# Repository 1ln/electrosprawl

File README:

Electrosprawl pcb

Hardware Design: 

Dan Olson 
Copyright 2019

This board is currently is testing phase, use at your own risk.

This board is designed as a testing platform for the cortex m4 samd51p20

Features:

Most pins broken out
Board can be attached to a raspberry pi 3 (board only, not pin header compatible)
Micro Sdcard slot
Micro usb available, 5v only

TODO:

Break out a few more pins if possible

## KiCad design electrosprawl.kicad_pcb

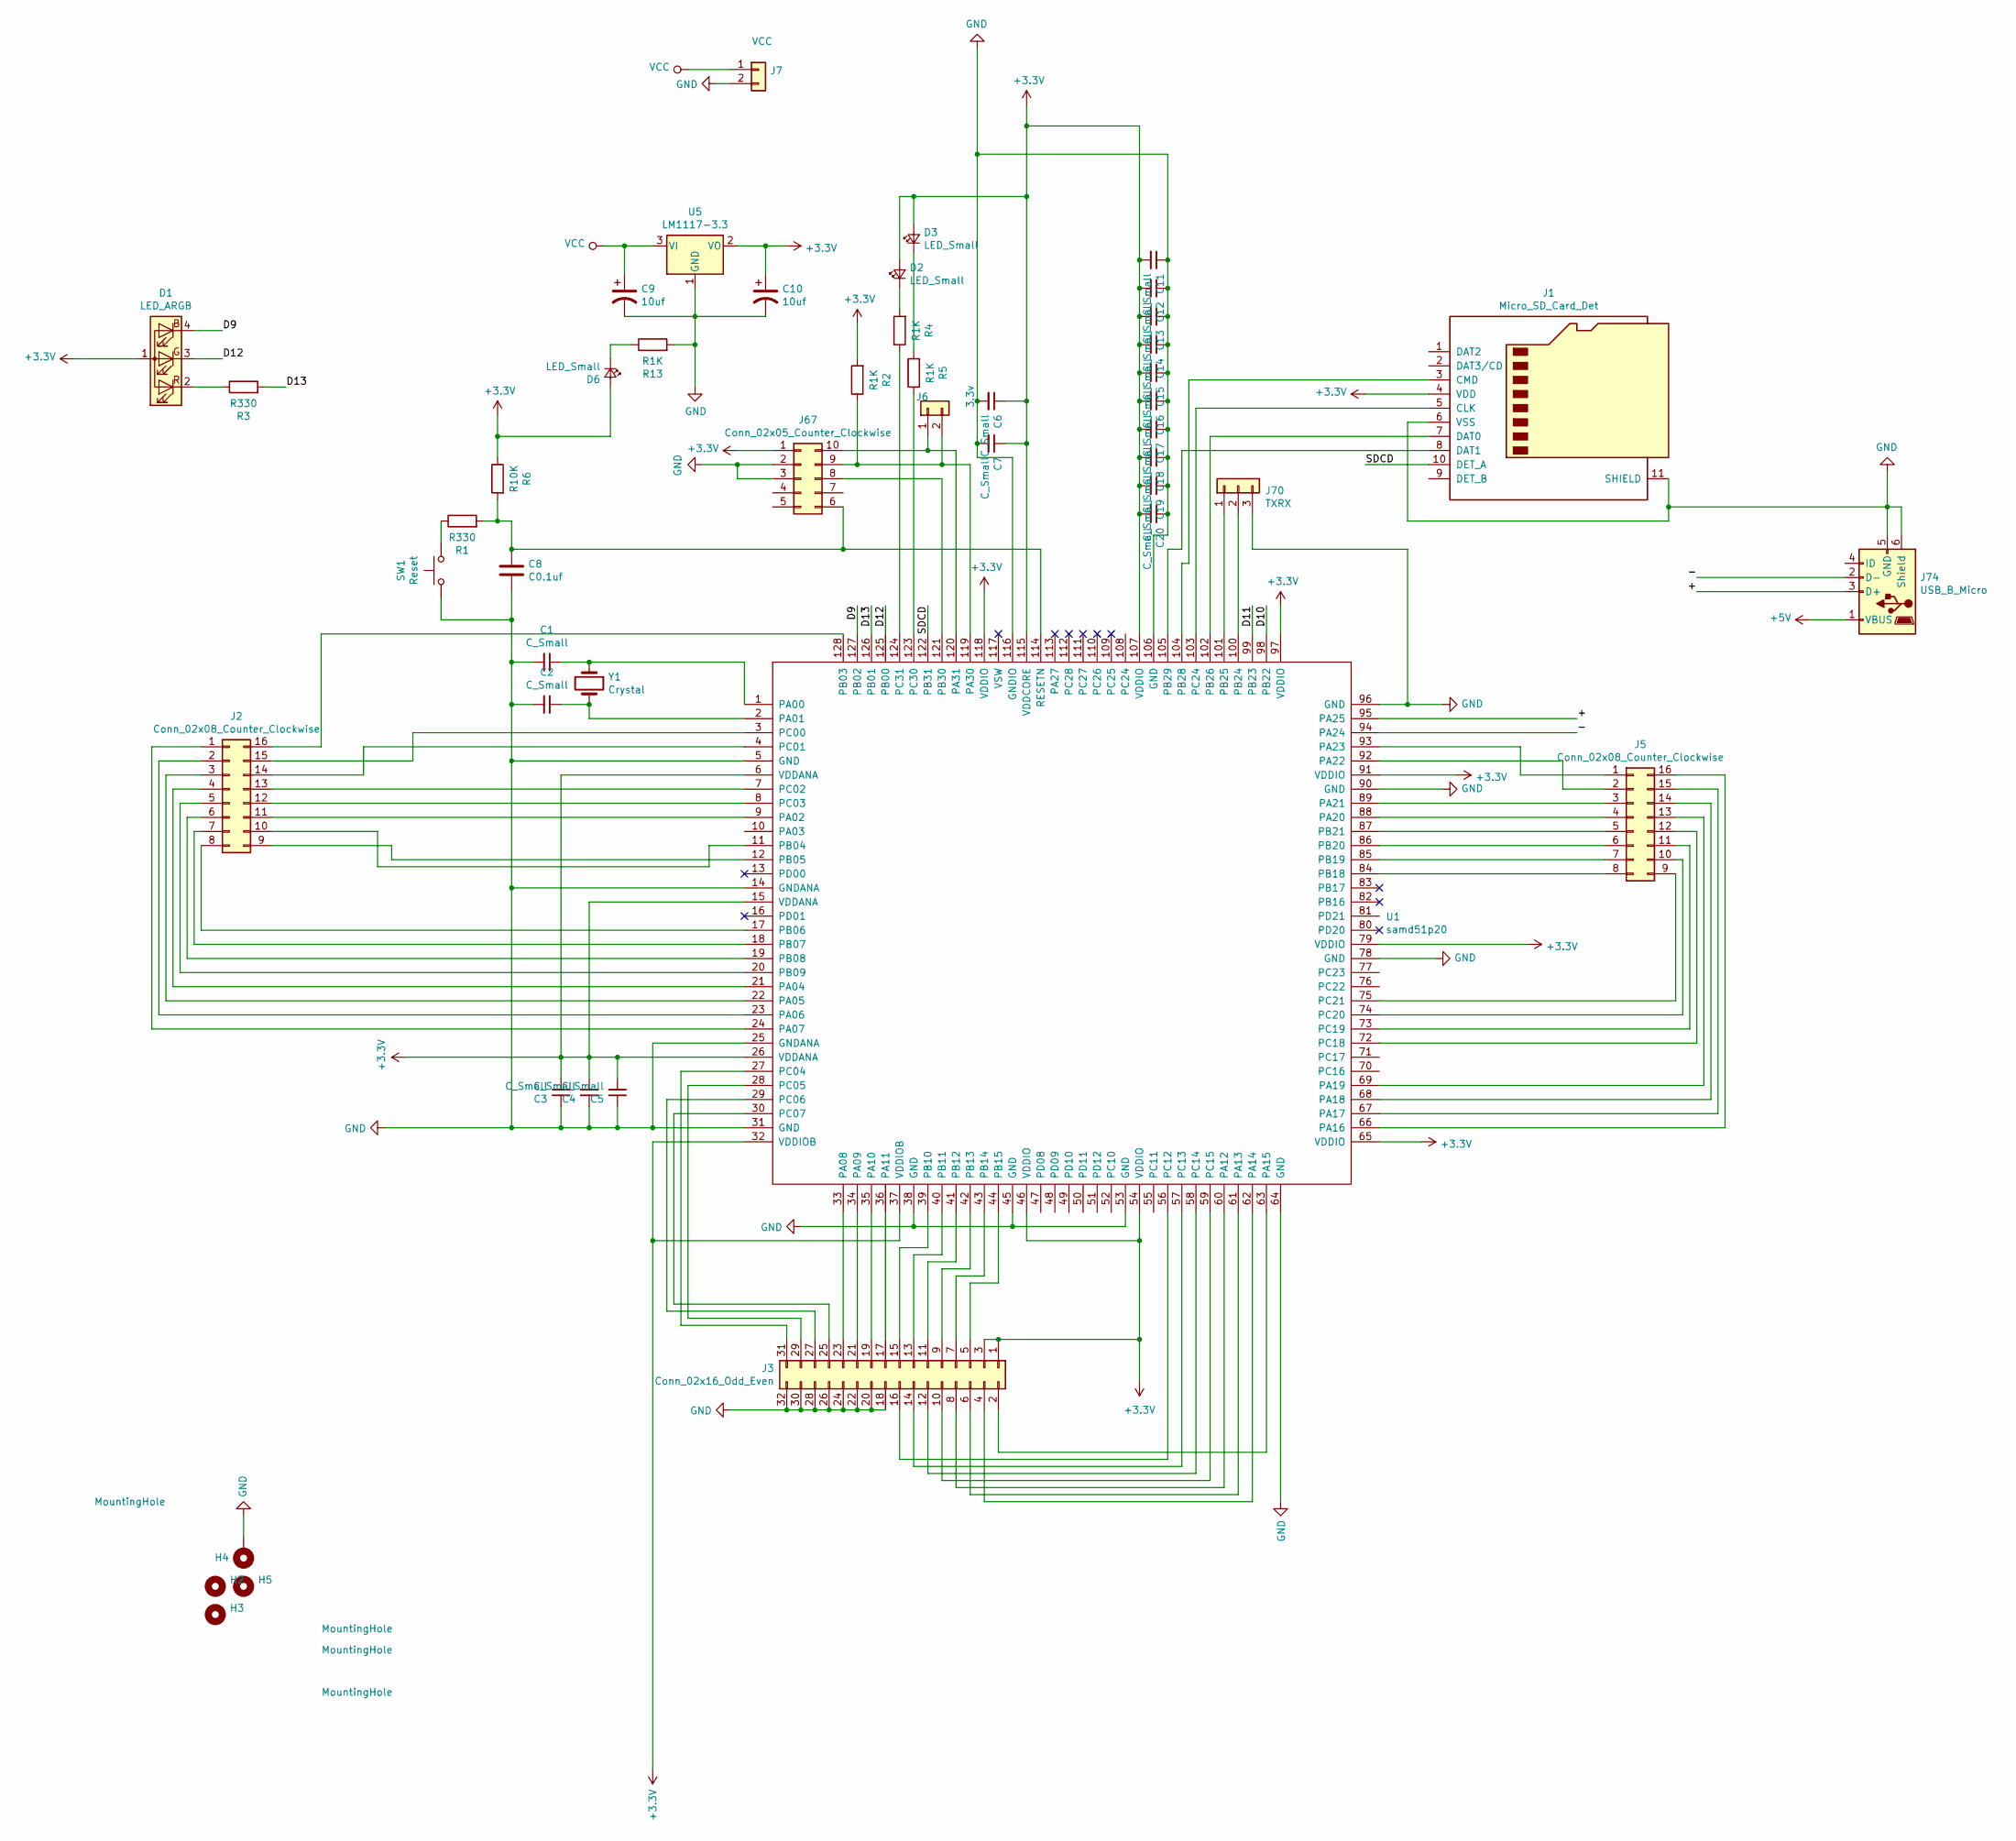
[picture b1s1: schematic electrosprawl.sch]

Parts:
C1, C2, C3, C4, C5, C6, C7, C11, C12, C13, C14, C15, C16, C17, C18, C19, C20: C_Small; C_0603_1608Metric
C8: C0.1uf; C_0603_1608Metric
C9: 10uf; CP_Elec_4x5.3
C10: 10uf; CP_Elec_4x4.5
D1: LED_ARGB; LED_RGB_5050-6
D2, D3, D6: LED_Small; LED_0603_1608Metric
H2, H3, H5: MountingHole; MountingHole_3mm
H4: MountingHole; MountingHole_3mm_Pad_Via
J1: Micro_SD_Card_Det; microSD_HC_Hirose_DM3D-SF
J2, J5: Conn_02x08_Counter_Clockwise; PinHeader_2x08_P2.54mm_Vertical
J3: Conn_02x16_Odd_Even; PinHeader_2x16_P2.54mm_Vertical
J6: 3.3v; PinHeader_1x02_P2.54mm_Vertical
J7: VCC; PinHeader_1x02_P2.54mm_Vertical
J67: Conn_02x05_Counter_Clockwise; PinHeader_2x05_P1.27mm_Vertical
J70: TXRX; PinHeader_1x03_P2.54mm_Vertical
J74: USB_B_Micro; USB_Micro-B_Amphenol_10103594-0001LF_Horizontal
R1, R3: R330; R_0603_1608Metric
R2, R4, R5, R13: R1K; R_0603_1608Metric
R6: R10K; R_0603_1608Metric
SW1: Reset; SW_SPST_EVPBF
U1: samd51p20; TQFP-128_14x14mm_P0.4mm
U5: LM1117-3.3; SOT-223
Y1: Crystal; Crystal_SMD_3215-2Pin_3.2x1.5mm

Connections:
+3V3: C3.2, C4.2, C5.2, C6.1, C7.1, C10.1, C11.2, C12.2, C13.2, C14.2, C15.2, C16.2, C17.2, C18.2, C19.2, C20.2, D1.1 (A), D2.2 (A), D3.2 (A), D6.2 (A), J1.4 (VDD), J3.1, J3.3, J67.1, R2.2, R6.1, U1.6 (VDDANA), U1.15 (VDDANA), U1.26 (VDDANA), U1.32 (VDDIOB), U1.37 (VDDIOB), U1.46 (VDDIO), U1.54 (VDDIO), U1.65 (VDDIO), U1.79 (VDDIO), U1.91 (VDDIO), U1.97 (VDDIO), U1.107 (VDDIO), U1.115 (VDDCORE), U1.118 (VDDIO), U5.2 (VO)
+5V: J74.1 (VBUS)
/+: J74.3 (D+), U1.95 (PA25)
/-: J74.2 (D-), U1.94 (PA24)
/D9: D1.4 (BK), U1.127 (PB02)
/D10: U1.98 (PB22)
/D11: U1.99 (PB23)
/D12: D1.3 (GK), U1.125 (PB00)
/D13: R3.2, U1.126 (PB01)
/SDCD: J1.10 (DET_A), U1.122 (PB31)
GND: C1.2, C2.2, C3.1, C4.1, C5.1, C6.2, C7.2, C8.2, C9.2, C10.2, C11.1, C12.1, C13.1, C14.1, C15.1, C16.1, C17.1, C18.1, C19.1, C20.1, H4.1, J1.6 (VSS), J1.11 (SHIELD), J3.18, J3.20, J3.22, J3.24, J3.26, J3.28, J3.30, J3.32, J7.2, J67.2, J67.3, J70.3, J74.5 (GND), J74.6 (Shield), R13.2, SW1.1, U1.5 (GND), U1.14 (GNDANA), U1.25 (GNDANA), U1.31 (GND), U1.38 (GND), U1.45 (GND), U1.53 (GND), U1.64 (GND), U1.78 (GND), U1.90 (GND), U1.96 (GND), U1.106 (GND), U1.116 (GNDIO), U5.1 (GND)
unnamed: C1.1, U1.1 (PA00), Y1.1
unnamed: C2.1, U1.2 (PA01), Y1.2
unnamed: C8.1, J67.6, R1.2, R6.2, U1.114 (RESETN)
unnamed: D1.2 (RK), R3.1
unnamed: D2.1 (K), R4.2
unnamed: D3.1 (K), R5.2
unnamed: D6.1 (K), R13.1
unnamed: J1.3 (CMD), U1.104 (PB28)
unnamed: J1.5 (CLK), U1.103 (PC24)
unnamed: J1.7 (DAT0), U1.102 (PB26)
unnamed: J1.8 (DAT1), U1.105 (PB29)
unnamed: J2.1, U1.24 (PA07)
unnamed: J2.2, U1.23 (PA06)
unnamed: J2.3, U1.22 (PA05)
unnamed: J2.4, U1.21 (PA04)
unnamed: J2.5, U1.20 (PB09)
unnamed: J2.6, U1.19 (PB08)
unnamed: J2.7, U1.18 (PB07)
unnamed: J2.8, U1.17 (PB06)
unnamed: J2.9, U1.12 (PB05)
unnamed: J2.10, U1.11 (PB04)
unnamed: J2.11, U1.9 (PA02)
unnamed: J2.12, U1.8 (PC03)
unnamed: J2.13, U1.7 (PC02)
unnamed: J2.14, U1.4 (PC01)
unnamed: J2.15, U1.3 (PC00)
unnamed: J2.16, U1.128 (PB03)
unnamed: J3.2, U1.63 (PA15)
unnamed: J3.4, U1.62 (PA14)
unnamed: J3.5, U1.44 (PB15)
unnamed: J3.6, U1.61 (PA13)
unnamed: J3.7, U1.43 (PB14)
unnamed: J3.8, U1.60 (PA12)
unnamed: J3.9, U1.42 (PB13)
unnamed: J3.10, U1.59 (PC15)
unnamed: J3.11, U1.41 (PB12)
unnamed: J3.12, U1.58 (PC14)
unnamed: J3.13, U1.40 (PB11)
unnamed: J3.14, U1.57 (PC13)
unnamed: J3.15, U1.39 (PB10)
unnamed: J3.16, U1.56 (PC12)
unnamed: J3.17, U1.36 (PA11)
unnamed: J3.19, U1.35 (PA10)
unnamed: J3.21, U1.34 (PA09)
unnamed: J3.23, U1.33 (PA08)
unnamed: J3.25, U1.30 (PC07)
unnamed: J3.27, U1.29 (PC06)
unnamed: J3.29, U1.28 (PC05)
unnamed: J3.31, U1.27 (PC04)
unnamed: J5.1, U1.93 (PA23)
unnamed: J5.2, U1.92 (PA22)
unnamed: J5.3, U1.89 (PA21)
unnamed: J5.4, U1.88 (PA20)
unnamed: J5.5, U1.87 (PB21)
unnamed: J5.6, U1.86 (PB20)
unnamed: J5.7, U1.85 (PB19)
unnamed: J5.8, U1.84 (PB18)
unnamed: J5.9, U1.75 (PC21)
unnamed: J5.10, U1.74 (PC20)
unnamed: J5.11, U1.73 (PC19)
unnamed: J5.12, U1.72 (PC18)
unnamed: J5.13, U1.69 (PA19)
unnamed: J5.14, U1.68 (PA18)
unnamed: J5.15, U1.67 (PA17)
unnamed: J5.16, U1.66 (PA16)
unnamed: J6.1, J67.10, U1.120 (PA31)
unnamed: J6.2, J67.9, R2.1, U1.119 (PA30)
unnamed: J67.8, U1.121 (PB30)
unnamed: J70.1, U1.101 (PB25)
unnamed: J70.2, U1.100 (PB24)
unnamed: R1.1, SW1.2
unnamed: R4.1, U1.124 (PC31)
unnamed: R5.1, U1.123 (PC30)
VCC: C9.1, J7.1, U5.3 (VI)

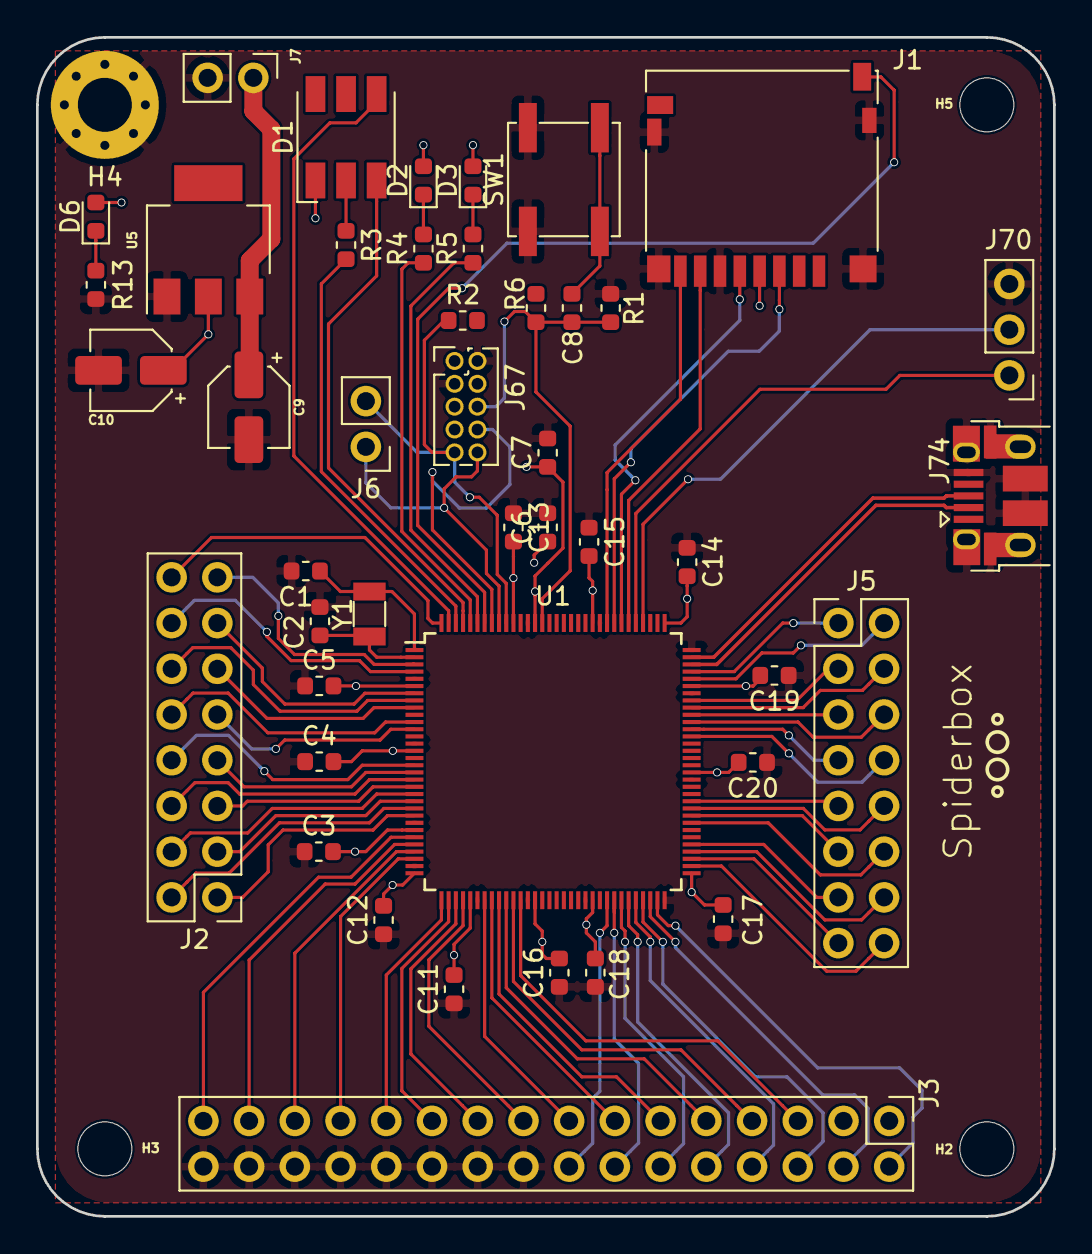
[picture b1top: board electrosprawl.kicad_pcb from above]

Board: 2 copper layers, 56.5 x 65.5 mm, 48 parts (0 on the bottom side), 82 nets.

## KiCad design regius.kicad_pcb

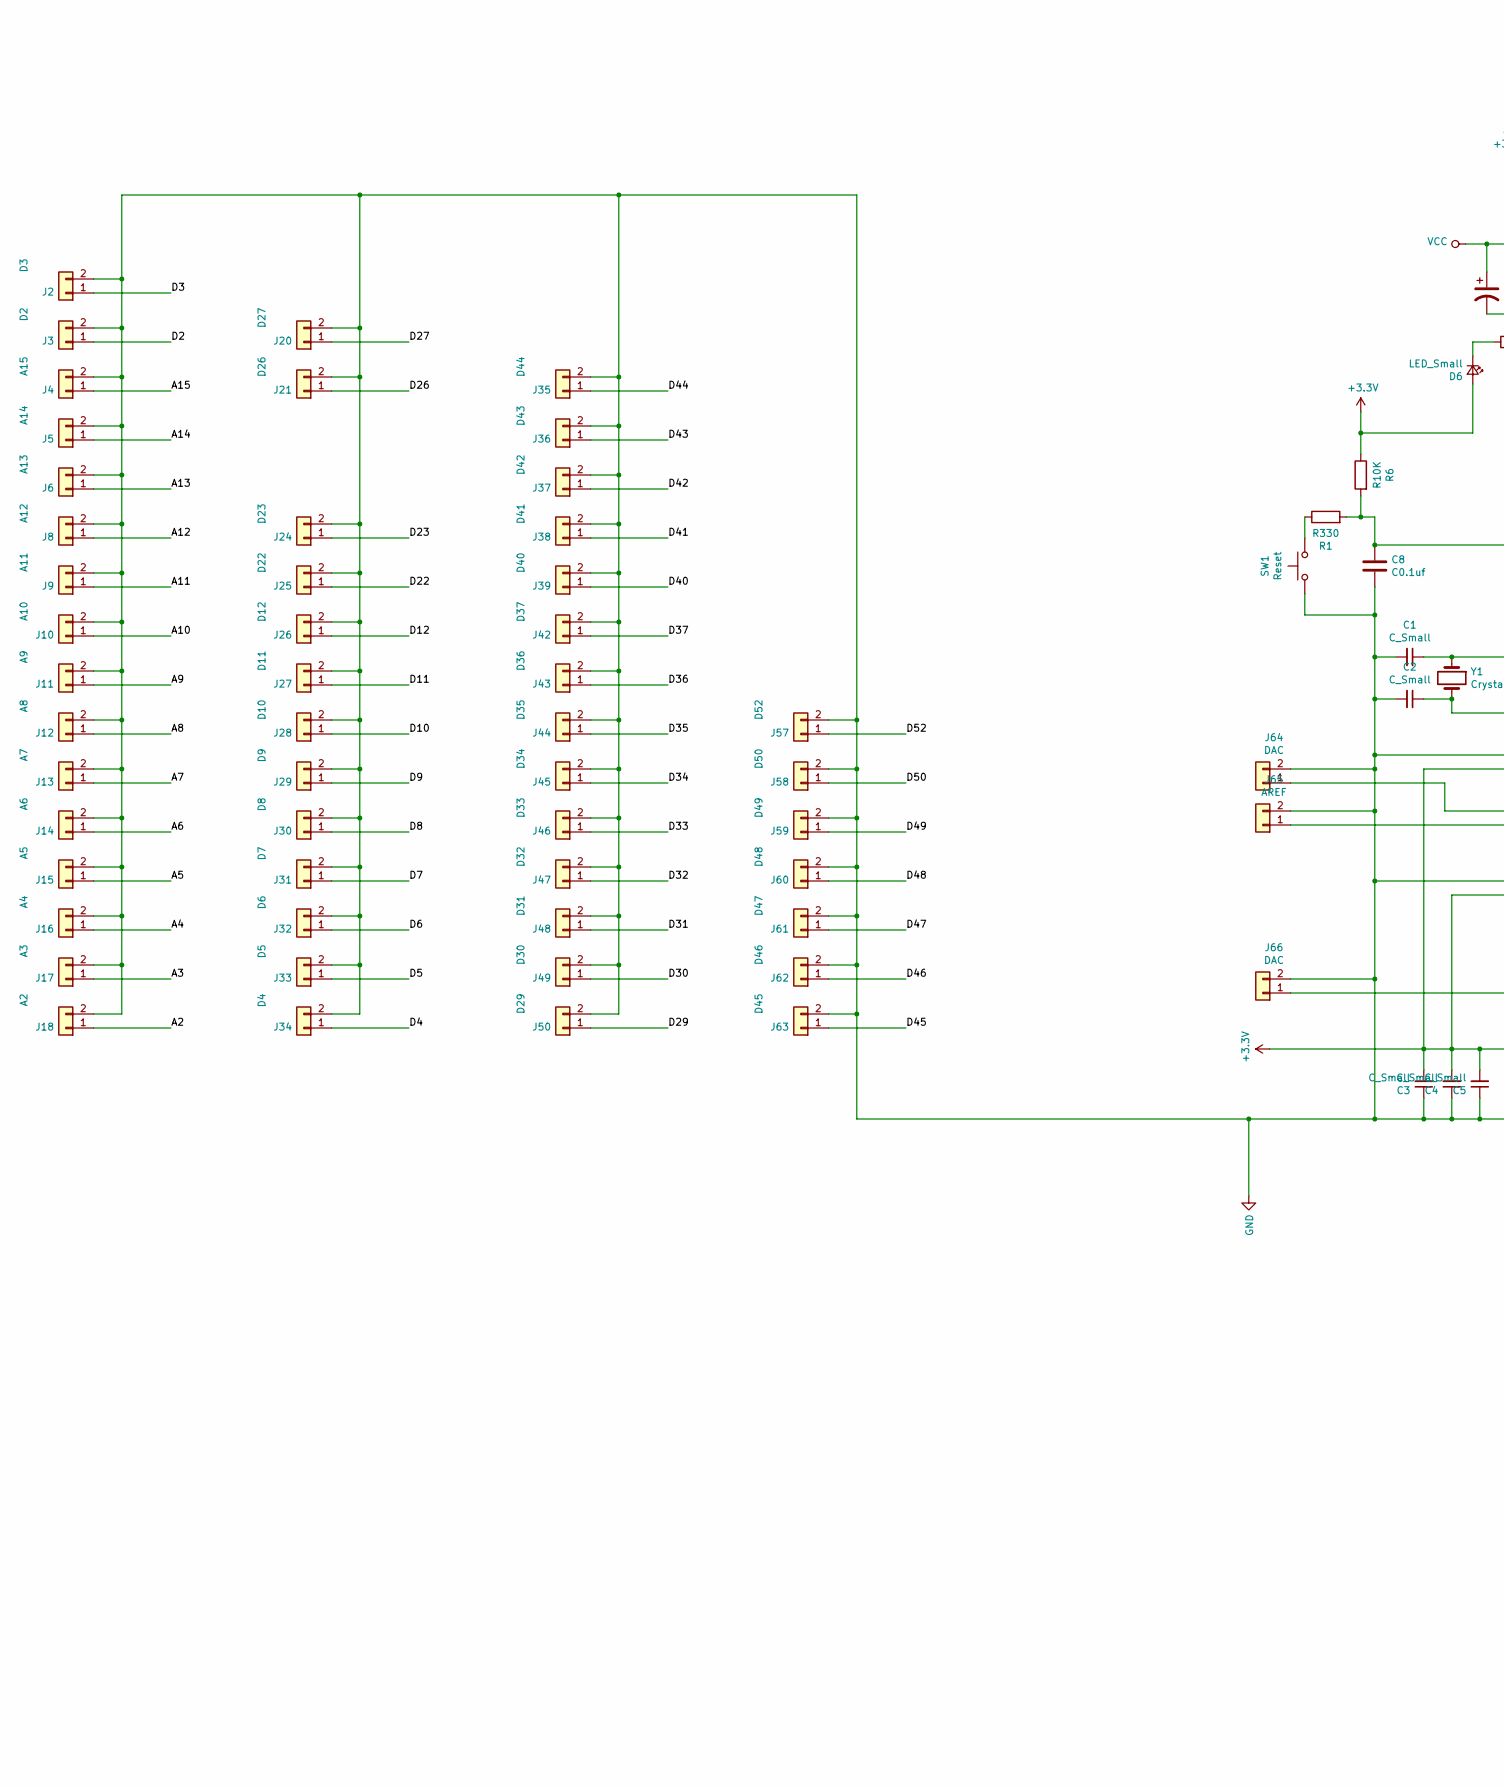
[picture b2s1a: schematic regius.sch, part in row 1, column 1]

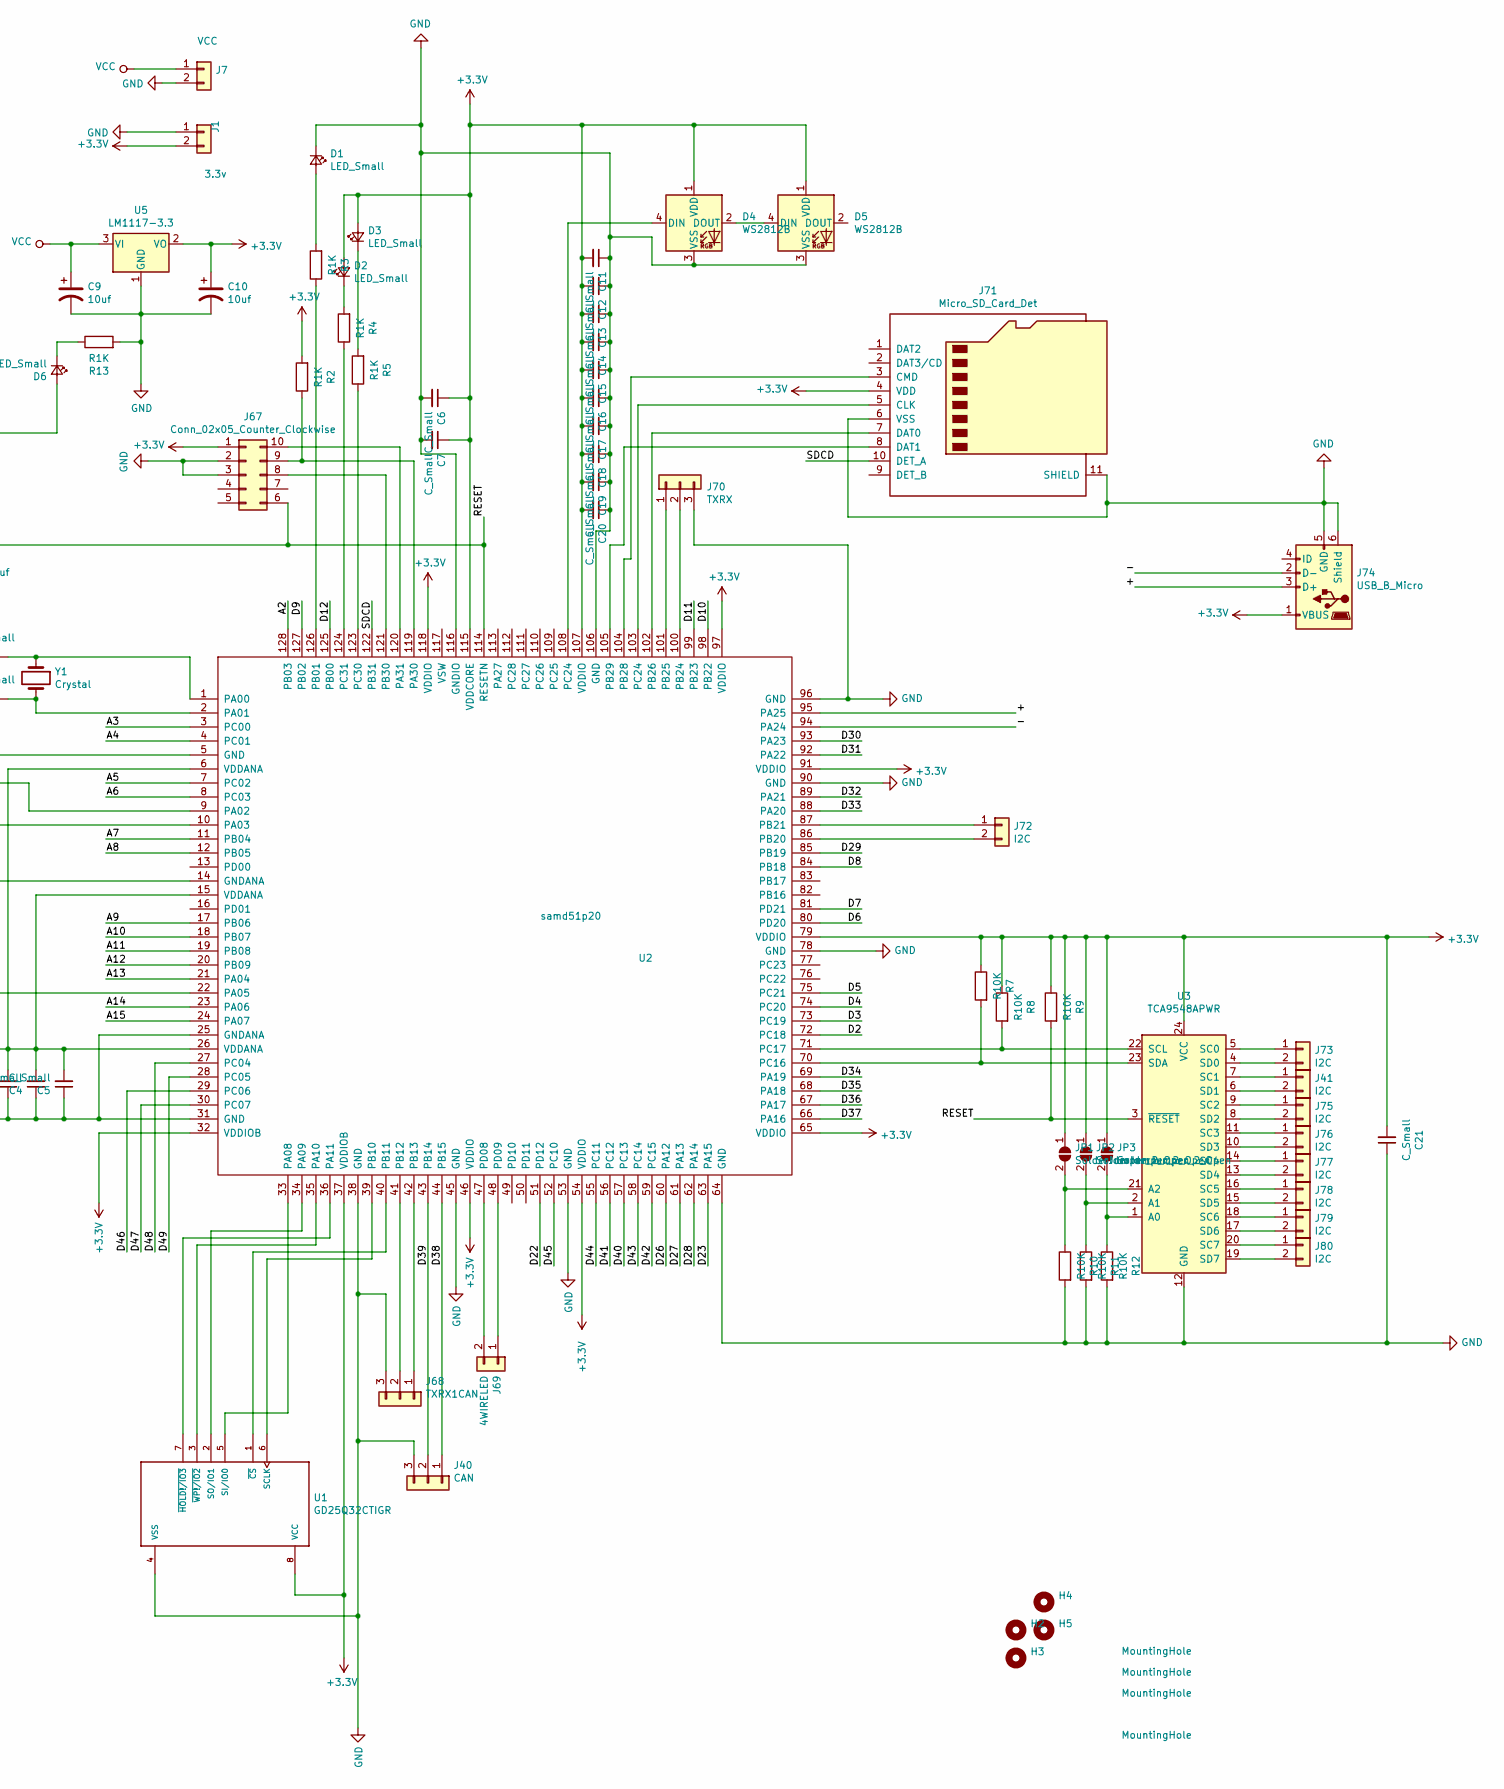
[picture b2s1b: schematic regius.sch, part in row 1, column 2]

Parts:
C1, C2, C3, C4, C5, C6, C7, C11, C12, C13, C14, C15, C16, C17, C18, C19, C20, C21: C_Small; C_0603_1608Metric
C8: C0.1uf; C_0603_1608Metric
C9: 10uf; CP_Elec_4x5.3
C10: 10uf; CP_Elec_4x4.5
D1, D2, D3, D6: LED_Small; LED_0603_1608Metric
D4, D5: WS2812B; LED_WS2812B_PLCC4_5.0x5.0mm_P3.2mm
H2, H3, H4, H5: MountingHole; MountingHole_3mm
J1: 3.3v; PinHeader_1x02_P2.54mm_Vertical
J2: D3; PinHeader_1x02_P2.54mm_Vertical
J3: D2; PinHeader_1x02_P2.54mm_Vertical
J4: A15; PinHeader_1x02_P2.54mm_Vertical
J5: A14; PinHeader_1x02_P2.54mm_Vertical
J6: A13; PinHeader_1x02_P2.54mm_Vertical
J7: VCC; PinHeader_1x02_P2.54mm_Vertical
J8: A12; PinHeader_1x02_P2.54mm_Vertical
J9: A11; PinHeader_1x02_P2.54mm_Vertical
J10: A10; PinHeader_1x02_P2.54mm_Vertical
J11: A9; PinHeader_1x02_P2.54mm_Vertical
J12: A8; PinHeader_1x02_P2.54mm_Vertical
J13: A7; PinHeader_1x02_P2.54mm_Vertical
J14: A6; PinHeader_1x02_P2.54mm_Vertical
J15: A5; PinHeader_1x02_P2.54mm_Vertical
J16: A4; PinHeader_1x02_P2.54mm_Vertical
J17: A3; PinHeader_1x02_P2.54mm_Vertical
J18: A2; PinHeader_1x02_P2.54mm_Vertical
J20: D27; PinHeader_1x02_P2.54mm_Vertical
J21: D26; PinHeader_1x02_P2.54mm_Vertical
J24: D23; PinHeader_1x02_P2.54mm_Vertical
J25: D22; PinHeader_1x02_P2.54mm_Vertical
J26: D12; PinHeader_1x02_P2.54mm_Vertical
J27: D11; PinHeader_1x02_P2.54mm_Vertical
J28: D10; PinHeader_1x02_P2.54mm_Vertical
J29: D9; PinHeader_1x02_P2.54mm_Vertical
J30: D8; PinHeader_1x02_P2.54mm_Vertical
J31: D7; PinHeader_1x02_P2.54mm_Vertical
J32: D6; PinHeader_1x02_P2.54mm_Vertical
J33: D5; PinHeader_1x02_P2.54mm_Vertical
J34: D4; PinHeader_1x02_P2.54mm_Vertical
J35: D44; PinHeader_1x02_P2.54mm_Vertical
J36: D43; PinHeader_1x02_P2.54mm_Vertical
J37: D42; PinHeader_1x02_P2.54mm_Vertical
J38: D41; PinHeader_1x02_P2.54mm_Vertical
J39: D40; PinHeader_1x02_P2.54mm_Vertical
J40: CAN; PinHeader_1x03_P2.54mm_Vertical
J41, J72, J73, J75, J76, J77, J78, J79, J80: I2C; PinHeader_1x02_P2.54mm_Vertical
J42: D37; PinHeader_1x02_P2.54mm_Vertical
J43: D36; PinHeader_1x02_P2.54mm_Vertical
J44: D35; PinHeader_1x02_P2.54mm_Vertical
J45: D34; PinHeader_1x02_P2.54mm_Vertical
J46: D33; PinHeader_1x02_P2.54mm_Vertical
J47: D32; PinHeader_1x02_P2.54mm_Vertical
J48: D31; PinHeader_1x02_P2.54mm_Vertical
J49: D30; PinHeader_1x02_P2.54mm_Vertical
J50: D29; PinHeader_1x02_P2.54mm_Vertical
J57: D52; PinHeader_1x02_P2.54mm_Vertical
J58: D50; PinHeader_1x02_P2.54mm_Vertical
J59: D49; PinHeader_1x02_P2.54mm_Vertical
J60: D48; PinHeader_1x02_P2.54mm_Vertical
J61: D47; PinHeader_1x02_P2.54mm_Vertical
J62: D46; PinHeader_1x02_P2.54mm_Vertical
J63: D45; PinHeader_1x02_P2.54mm_Vertical
J64, J66: DAC; PinHeader_1x02_P2.54mm_Vertical
J65: AREF; PinHeader_1x02_P2.54mm_Vertical
J67: Conn_02x05_Counter_Clockwise; PinHeader_2x05_P1.27mm_Vertical
J68: TXRX1CAN; PinHeader_1x03_P2.54mm_Vertical
J69: 4WIRELED; PinHeader_1x02_P2.54mm_Vertical
J70: TXRX; PinHeader_1x03_P2.54mm_Vertical
J71: Micro_SD_Card_Det; microSD_HC_Hirose_DM3D-SF
J74: USB_B_Micro; USB_Micro-B_Amphenol_10103594-0001LF_Horizontal
JP1, JP2, JP3: SolderJumper_2_Open; SolderJumper-2_P1.3mm_Open_RoundedPad1.0x1.5mm
R1: R330; R_0603_1608Metric
R2, R3, R4, R5, R13: R1K; R_0603_1608Metric
R6, R7, R8, R9, R10, R11, R12: R10K; R_0603_1608Metric
SW1: Reset; SW_SPST_EVPBF
U1: GD25Q32CTIGR; SOIC127P600X175-8N
U2: samd51p20; TQFP-128_14x14mm_P0.4mm
U3: TCA9548APWR; TSSOP-24_4.4x7.8mm_P0.65mm
U5: LM1117-3.3; SOT-223
Y1: Crystal; Crystal_SMD_3215-2Pin_3.2x1.5mm

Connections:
+3V3: C3.2, C4.2, C5.2, C6.1, C7.1, C10.1, C11.2, C12.2, C13.2, C14.2, C15.2, C16.2, C17.2, C18.2, C19.2, C20.2, C21.2, D2.2 (A), D3.2 (A), D4.1 (VDD), D5.1 (VDD), D6.2 (A), J1.2, J67.1, J71.4 (VDD), J74.1 (VBUS), JP1.1 (A), JP2.1 (A), JP3.1 (A), R2.2, R6.1, R7.1, R8.1, R9.1, U1.8 (VCC), U2.6 (VDDANA), U2.15 (VDDANA), U2.26 (VDDANA), U2.32 (VDDIOB), U2.37 (VDDIOB), U2.46 (VDDIO), U2.54 (VDDIO), U2.65 (VDDIO), U2.79 (VDDIO), U2.91 (VDDIO), U2.97 (VDDIO), U2.107 (VDDIO), U2.115 (VDDCORE), U2.118 (VDDIO), U3.24 (VCC), U5.2 (VO)
/+: J74.3 (D+), U2.95 (PA25)
/-: J74.2 (D-), U2.94 (PA24)
/A2: J18.1, U2.128 (PB03)
/A3: J17.1, U2.3 (PC00)
/A4: J16.1, U2.4 (PC01)
/A5: J15.1, U2.7 (PC02)
/A6: J14.1, U2.8 (PC03)
/A7: J13.1, U2.11 (PB04)
/A8: J12.1, U2.12 (PB05)
/A9: J11.1, U2.17 (PB06)
/A10: J10.1, U2.18 (PB07)
/A11: J9.1, U2.19 (PB08)
/A12: J8.1, U2.20 (PB09)
/A13: J6.1, U2.21 (PA04)
/A14: J5.1, U2.23 (PA06)
/A15: J4.1, U2.24 (PA07)
/D2: J3.1, U2.72 (PC18)
/D3: J2.1, U2.73 (PC19)
/D4: J34.1, U2.74 (PC20)
/D5: J33.1, U2.75 (PC21)
/D6: J32.1, U2.80 (PD20)
/D7: J31.1, U2.81 (PD21)
/D8: J30.1, U2.84 (PB18)
/D9: J29.1, U2.127 (PB02)
/D10: J28.1, U2.98 (PB22)
/D11: J27.1, U2.99 (PB23)
/D12: J26.1, U2.125 (PB00)
/D22: J25.1, U2.51 (PD12)
/D23: J24.1, U2.63 (PA15)
/D26: J21.1, U2.60 (PA12)
/D27: J20.1, U2.61 (PA13)
/D28: U2.62 (PA14); also elsewhere on the board
/D29: J50.1, U2.85 (PB19)
/D30: J49.1, U2.93 (PA23)
/D31: J48.1, U2.92 (PA22)
/D32: J47.1, U2.89 (PA21)
/D33: J46.1, U2.88 (PA20)
/D34: J45.1, U2.69 (PA19)
/D35: J44.1, U2.68 (PA18)
/D36: J43.1, U2.67 (PA17)
/D37: J42.1, U2.66 (PA16)
/D38: J40.1, U2.44 (PB15)
/D39: J40.2, U2.43 (PB14)
/D40: J39.1, U2.57 (PC13)
/D41: J38.1, U2.56 (PC12)
/D42: J37.1, U2.59 (PC15)
/D43: J36.1, U2.58 (PC14)
/D44: J35.1, U2.55 (PC11)
/D45: J63.1, U2.52 (PC10)
/D46: J62.1, U2.29 (PC06)
/D47: J61.1, U2.30 (PC07)
/D48: J60.1, U2.27 (PC04)
/D49: J59.1, U2.28 (PC05)
/D50: J58.1
/D52: J57.1
/SDCD: J71.10 (DET_A), U2.122 (PB31)
GND: C1.2, C2.2, C3.1, C4.1, C5.1, C6.2, C7.2, C8.2, C9.2, C10.2, C11.1, C12.1, C13.1, C14.1, C15.1, C16.1, C17.1, C18.1, C19.1, C20.1, C21.1, D1.1 (K), D4.3 (VSS), D5.3 (VSS), J1.1, J2.2, J3.2, J4.2, J5.2, J6.2, J7.2, J8.2, J9.2, J10.2, J11.2, J12.2, J13.2, J14.2, J15.2, J16.2, J17.2, J18.2, J20.2, J21.2, J24.2, J25.2, J26.2, J27.2, J28.2, J29.2, J30.2, J31.2, J32.2, J33.2, J34.2, J35.2, J36.2, J37.2, J38.2, J39.2, J40.3, J42.2, J43.2, J44.2, J45.2, J46.2, J47.2, J48.2, J49.2, J50.2, J57.2, J58.2, J59.2, J60.2, J61.2, J62.2, J63.2, J64.2, J65.2, J66.2, J67.2, J67.3, J68.3, J70.3, J71.6 (VSS), J71.11 (SHIELD), J74.5 (GND), J74.6 (Shield), R10.2, R11.2, R12.2, R13.2, SW1.1, U1.4 (VSS), U2.5 (GND), U2.14 (GNDANA), U2.25 (GNDANA), U2.31 (GND), U2.38 (GND), U2.45 (GND), U2.53 (GND), U2.64 (GND), U2.78 (GND), U2.90 (GND), U2.96 (GND), U2.106 (GND), U2.116 (GNDIO), U3.12 (GND), U5.1 (GND); also elsewhere on the board
unnamed: C1.1, U2.1 (PA00), Y1.1
unnamed: C2.1, U2.2 (PA01), Y1.2
unnamed: D1.2 (A), R3.2
unnamed: D2.1 (K), R4.2
unnamed: D3.1 (K), R5.2
unnamed: D4.2 (DOUT), D5.4 (DIN)
unnamed: D4.4 (DIN), U2.108 (PC24)
unnamed: D6.1 (K), R13.1
unnamed: J41.1, U3.7 (SC1)
unnamed: J41.2, U3.6 (SD1)
unnamed: J64.1, U2.9 (PA02)
unnamed: J65.1, U2.10 (PA03)
unnamed: J66.1, U2.22 (PA05)
unnamed: J67.8, U2.121 (PB30)
unnamed: J67.9, R2.1, U2.119 (PA30)
unnamed: J67.10, U2.120 (PA31)
unnamed: J68.1, U2.42 (PB13)
unnamed: J68.2, U2.41 (PB12)
unnamed: J69.1, U2.48 (PD09)
unnamed: J69.2, U2.47 (PD08)
unnamed: J70.1, U2.101 (PB25)
unnamed: J70.2, U2.100 (PB24)
unnamed: J71.3 (CMD), U2.104 (PB28)
unnamed: J71.5 (CLK), U2.103 (PC24)
unnamed: J71.7 (DAT0), U2.102 (PB26)
unnamed: J71.8 (DAT1), U2.105 (PB29)
unnamed: J72.1, U2.87 (PB21)
unnamed: J72.2, U2.86 (PB20)
unnamed: J73.1, U3.5 (SC0)
unnamed: J73.2, U3.4 (SD0)
unnamed: J75.1, U3.9 (SC2)
unnamed: J75.2, U3.8 (SD2)
unnamed: J76.1, U3.11 (SC3)
unnamed: J76.2, U3.10 (SD3)
unnamed: J77.1, U3.14 (SC4)
unnamed: J77.2, U3.13 (SD4)
unnamed: J78.1, U3.16 (SC5)
unnamed: J78.2, U3.15 (SD5)
unnamed: J79.1, U3.18 (SC6)
unnamed: J79.2, U3.17 (SD6)
unnamed: J80.1, U3.20 (SC7)
unnamed: J80.2, U3.19 (SD7)
unnamed: JP1.2 (B), R10.1, U3.21 (A2)
unnamed: JP2.2 (B), R11.1, U3.2 (A1)
unnamed: JP3.2 (B), R12.1, U3.1 (A0)
unnamed: R1.1, SW1.2
unnamed: R3.1, U2.126 (PB01)
unnamed: R4.1, U2.124 (PC31)
unnamed: R5.1, U2.123 (PC30)
unnamed: R7.2, U2.70 (PC16), U3.23 (SDA)
unnamed: R8.2, U2.71 (PC17), U3.22 (SCL)
unnamed: U1.1 (~CS~), U2.40 (PB11)
unnamed: U1.2 (SO/IO1), U2.34 (PA09)
unnamed: U1.3 (~WP!/IO2~), U2.35 (PA10)
unnamed: U1.5 (SI/IO0), U2.33 (PA08)
unnamed: U1.6 (SCLK), U2.39 (PB10)
unnamed: U1.7 (~HOLD!/IO3~), U2.36 (PA11)
VCC: C9.1, J7.1, U5.3 (VI)

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
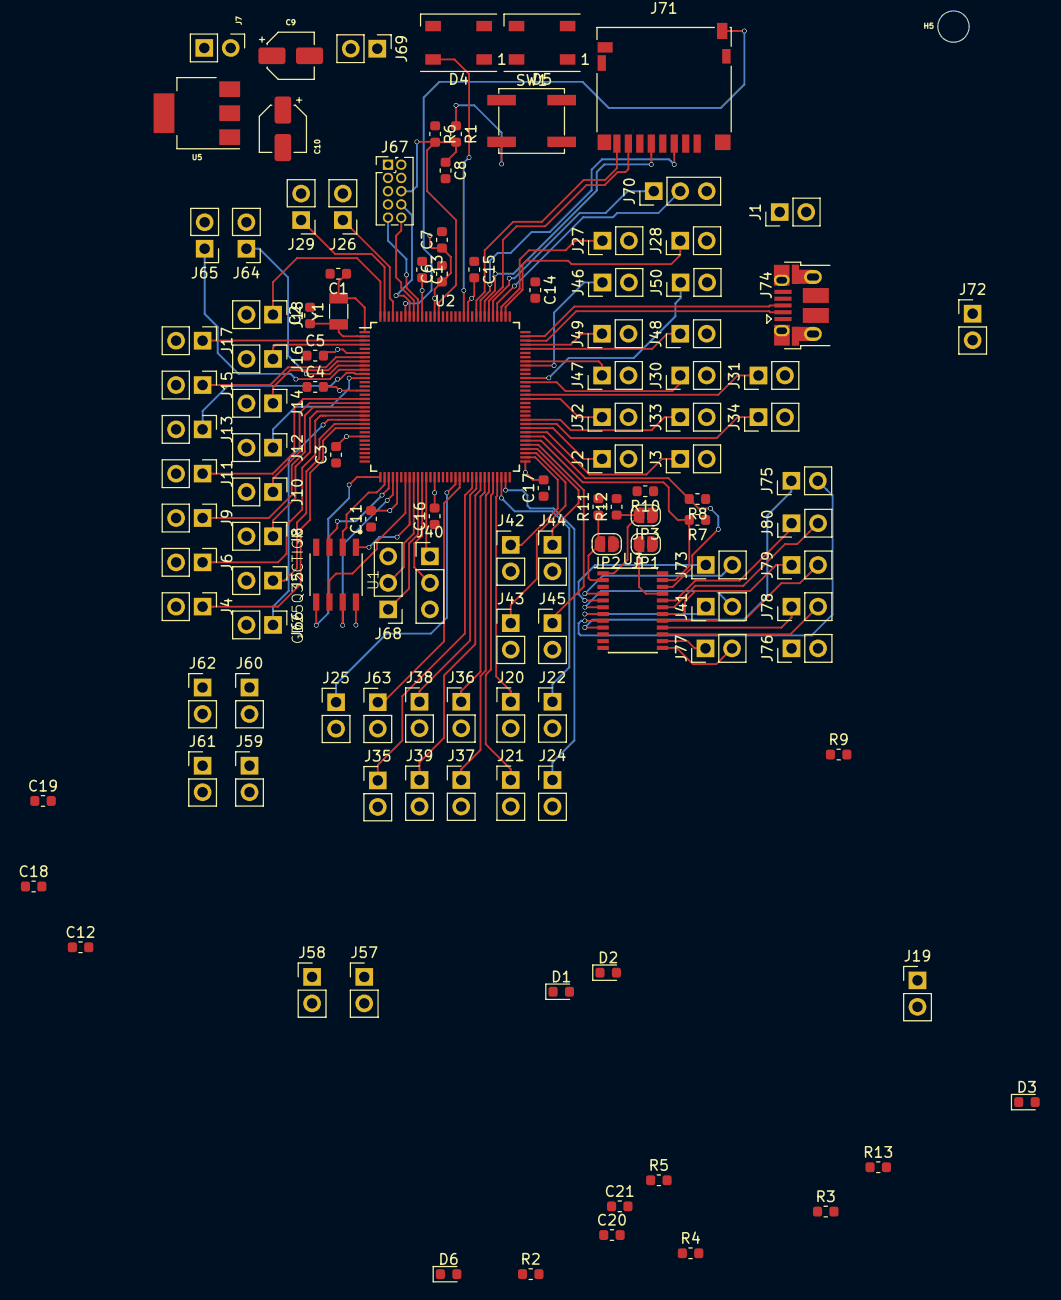
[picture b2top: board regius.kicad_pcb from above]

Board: 2 copper layers, 126 parts (0 on the bottom side), 116 nets.

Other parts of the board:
J19: reset; PinHeader_1x02_P2.54mm_Vertical
J22: D28; PinHeader_1x02_P2.54mm_Vertical

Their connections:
/D28: J22.1; also elsewhere on the board
GND: J19.2, J22.2; also elsewhere on the board

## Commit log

2019-03-29 update schematic
2019-03-29 debug port
2019-03-30 update design
2019-03-31 add footprints
2019-03-31 add 3d image
2019-04-02 update schematic tca9548
2019-04-02 update layout design
2019-04-03 update layout
2019-04-06 rename project
2019-04-06 update i2c with sx1509
2019-04-07 update layout redesign
2019-04-15 complete iteration 1
2019-04-15 update redesign
2019-05-07 add rgb led
2019-05-13 add README
